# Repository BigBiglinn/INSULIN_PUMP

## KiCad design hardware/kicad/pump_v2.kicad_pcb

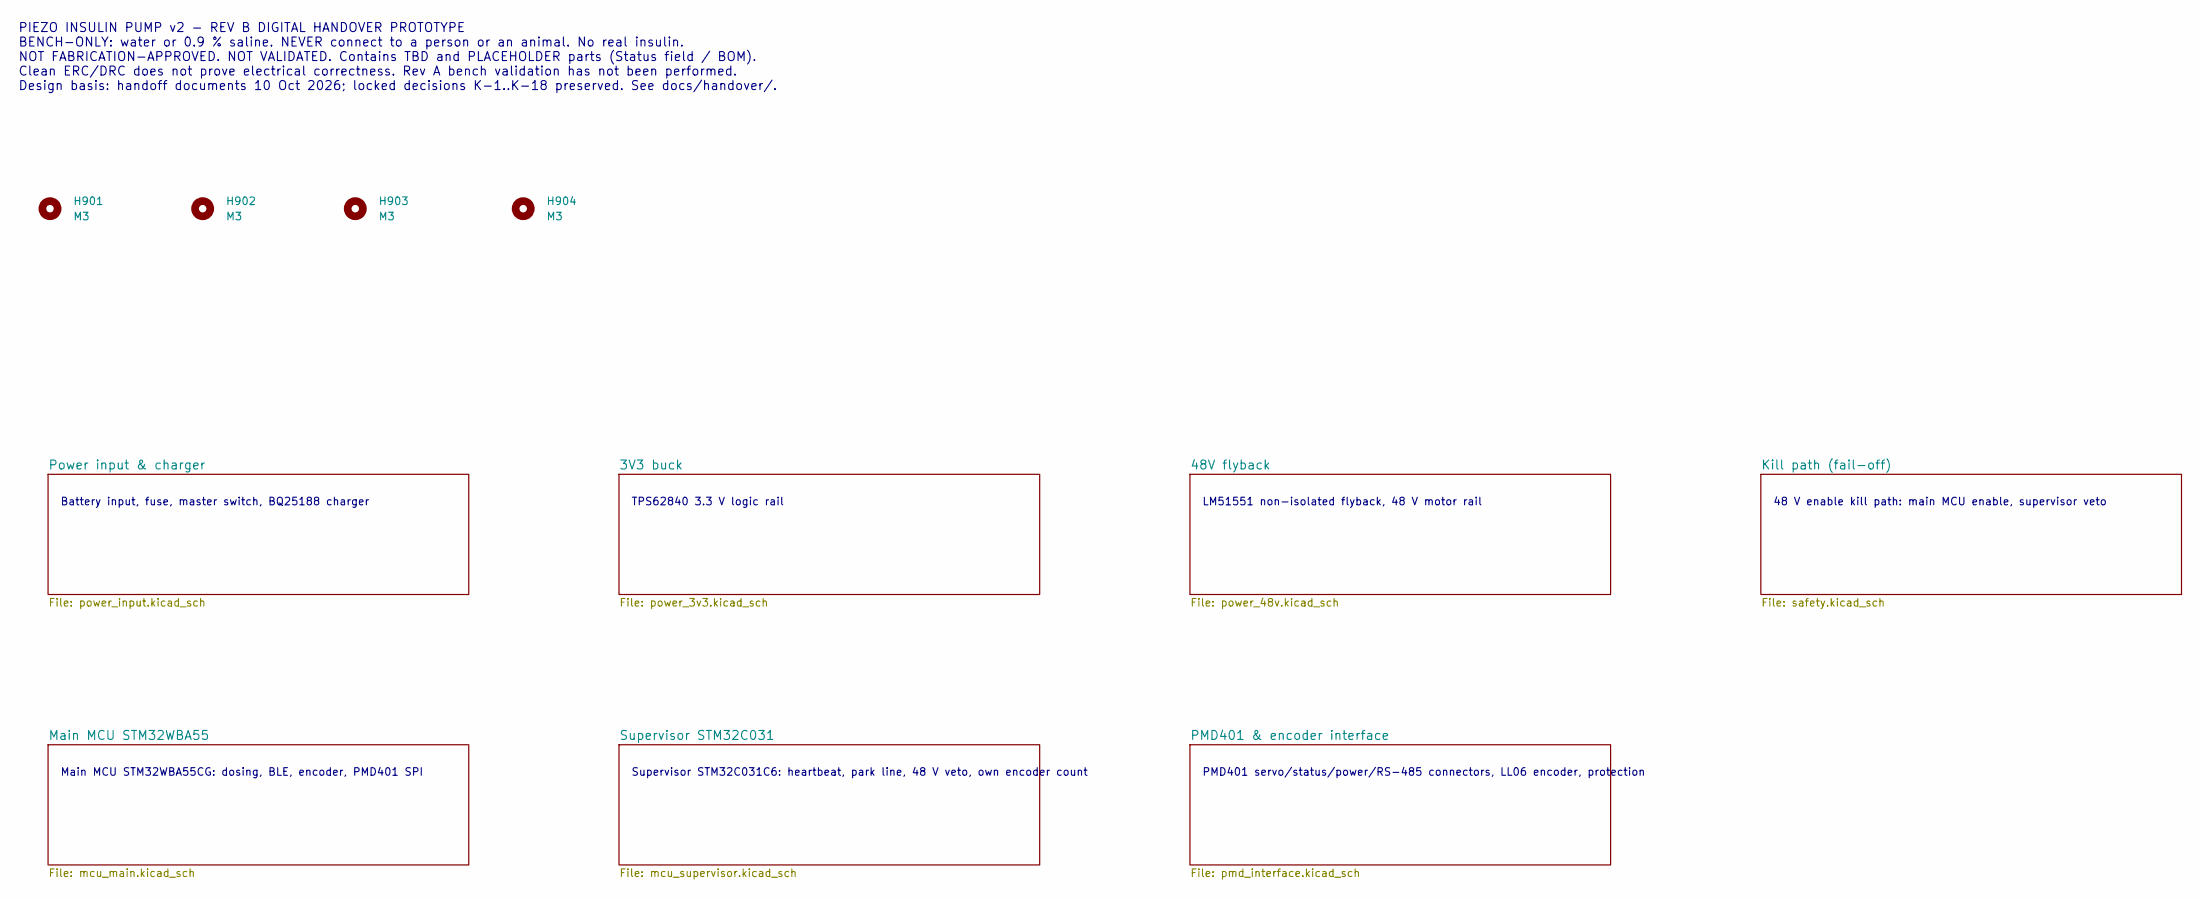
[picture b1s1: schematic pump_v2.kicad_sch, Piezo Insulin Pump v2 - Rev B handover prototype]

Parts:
H901, H902, H903, H904: M3; MountingHole_3.2mm_M3

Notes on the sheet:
PIEZO INSULIN PUMP v2 - REV B DIGITAL HANDOVER PROTOTYPE BENCH-ONLY: water or 0.9 % saline. NEVER connect to a person or an animal. No real insulin. NOT FABRICATION-APPROVED. NOT VALIDATED. Contains TBD and PLACEHOLDER parts (Status field / BOM). Clean ERC/DRC does not prove electrical correctness.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
Battery input, fuse, master switch, BQ25188 charger
TPS62840 3.3 V logic rail
LM51551 non-isolated flyback, 48 V motor rail
48 V enable kill path: main MCU enable, supervisor veto
Main MCU STM32WBA55CG: dosing, BLE, encoder, PMD401 SPI
Supervisor STM32C031C6: heartbeat, park line, 48 V veto, own encoder count
PMD401 servo/status/power/RS-485 connectors, LL06 encoder, protection

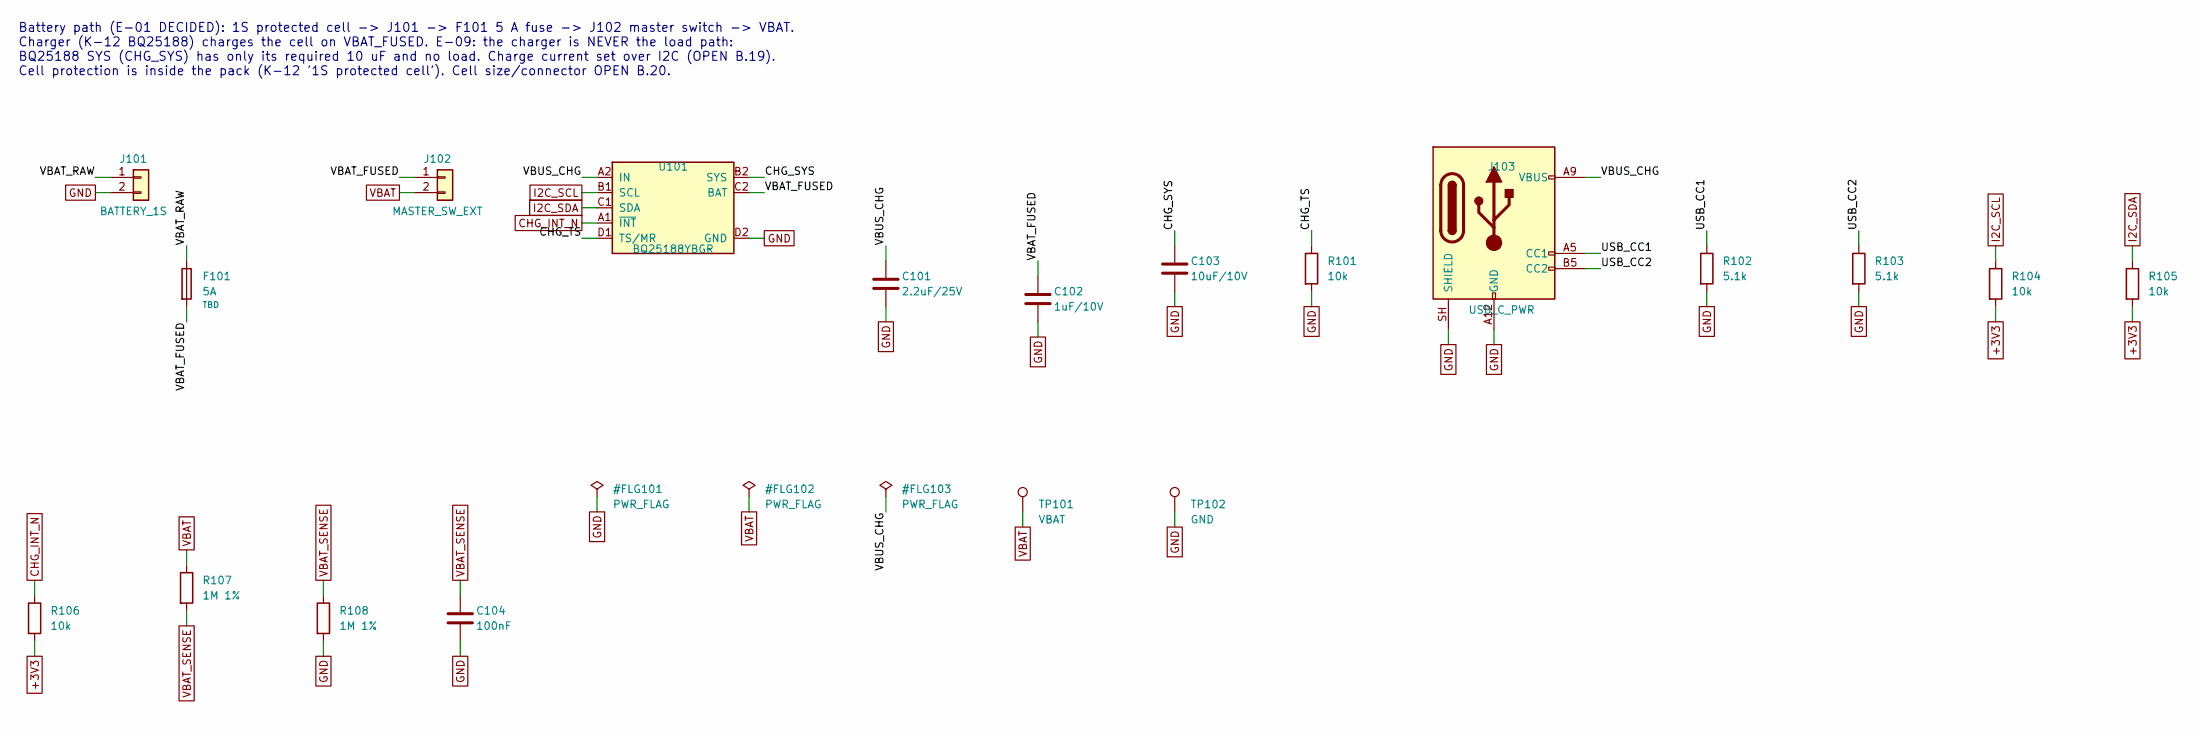
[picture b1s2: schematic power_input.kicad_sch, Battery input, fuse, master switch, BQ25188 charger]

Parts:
C101: 2.2uF/25V; C_0805_2012Metric
C102: 1uF/10V; C_0603_1608Metric
C103: 10uF/10V; C_0805_2012Metric
C104: 100nF; C_0603_1608Metric
F101: 5A; Fuse_2920_7451Metric
J101: BATTERY_1S; AMASS_XT30PW-M_1x02_P2.50mm_Horizontal; MPN AMASS XT30PW-M
J102: MASTER_SW_EXT; TerminalBlock_Phoenix_MKDS-1,5-2-5.08_1x02_P5.08mm_Horizont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
J103: USB_C_PWR; USB_C_Receptacle_GCT_USB4125-xx-x_6P_TopMnt_Horizontal; MPN GCT USB4125
R101, R104, R105, R106: 10k; R_0603_1608Metric
R102, R103: 5.1k; R_0603_1608Metric
R107, R108: 1M 1%; R_0603_1608Metric
TP101: VBAT; TestPoint_Pad_D1.0mm
TP102: GND; TestPoint_Pad_D1.0mm
U101: BQ25188YBGR; TI_YBG0008_DSBGA-8_P0.4mm; MPN BQ25188YBGR

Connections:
+3V3: R104.2, R105.2, R106.2; also elsewhere on the board
/Power input & charger/CHG_SYS: C103.1, U101.B2 (SYS)
/Power input & charger/CHG_TS: R101.1, U101.D1 (TS/MR)
/Power input & charger/USB_CC1: J103.A5 (CC1), R102.1
/Power input & charger/USB_CC2: J103.B5 (CC2), R103.1
/Power input & charger/VBAT_FUSED: C102.1, F101.2, J102.1, U101.C2 (BAT)
/Power input & charger/VBAT_RAW: F101.1, J101.1
/Power input & charger/VBUS_CHG: C101.1, J103.A9 (VBUS), J103.B9 (VBUS), U101.A2 (IN)
CHG_INT_N: R106.1, U101.A1 (~INT); also elsewhere on the board
I2C_SCL: R104.1, U101.B1 (SCL); also elsewhere on the board
I2C_SDA: R105.1, U101.C1 (SDA); also elsewhere on the board
VBAT_SENSE: C104.1, R107.2, R108.1; also elsewhere on the board

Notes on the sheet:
Battery path (E-01 DECIDED): 1S protected cell -> J101 -> F101 5 A fuse -> J102 master switch -> VBAT. Charger (K-12 BQ25188) charges the cell on VBAT_FUSED. E-09: the charger is NEVER the load path: BQ25188 SYS (CHG_SYS) has only its required 10 uF and no load. Charge current set over I2C (OPEN B.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

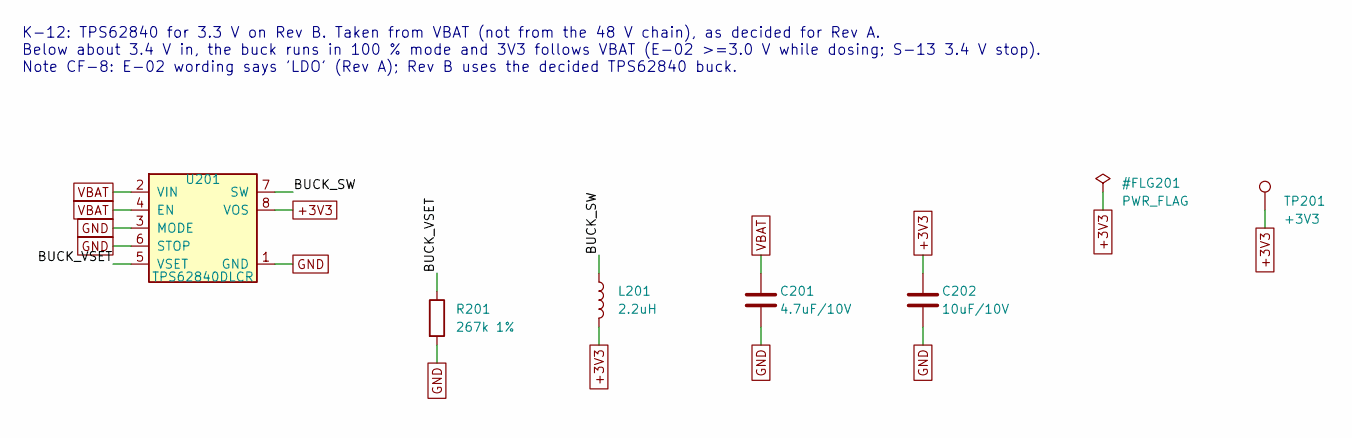
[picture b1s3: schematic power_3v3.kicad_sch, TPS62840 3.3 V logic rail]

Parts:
C201: 4.7uF/10V; C_0603_1608Metric
C202: 10uF/10V; C_0805_2012Metric
L201: 2.2uH; L_0603_1608Metric
R201: 267k 1%; R_0603_1608Metric
TP201: +3V3; TestPoint_Pad_D1.0mm
U201: TPS62840DLCR; Texas_VSON-HR-8_1.5x2mm_P0.5mm; MPN TPS62840DLCR

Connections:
+3V3: C202.1, L201.2, TP201.1, U201.8 (VOS); also elsewhere on the board
/3V3 buck/BUCK_SW: L201.1, U201.7 (SW)
/3V3 buck/BUCK_VSET: R201.1, U201.5 (VSET)

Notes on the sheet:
K-12: TPS62840 for 3.3 V on Rev B. Taken from VBAT (not from the 48 V chain), as decided for Rev A. Below about 3.4 V in, the buck runs in 100 % mode and 3V3 follows VBAT (E-02 >=3.0 V while dosing; S-13 3.4 V stop). Note CF-8: E-02 wording says 'LDO' (Rev A); Rev B uses the decided TPS62840 buck.

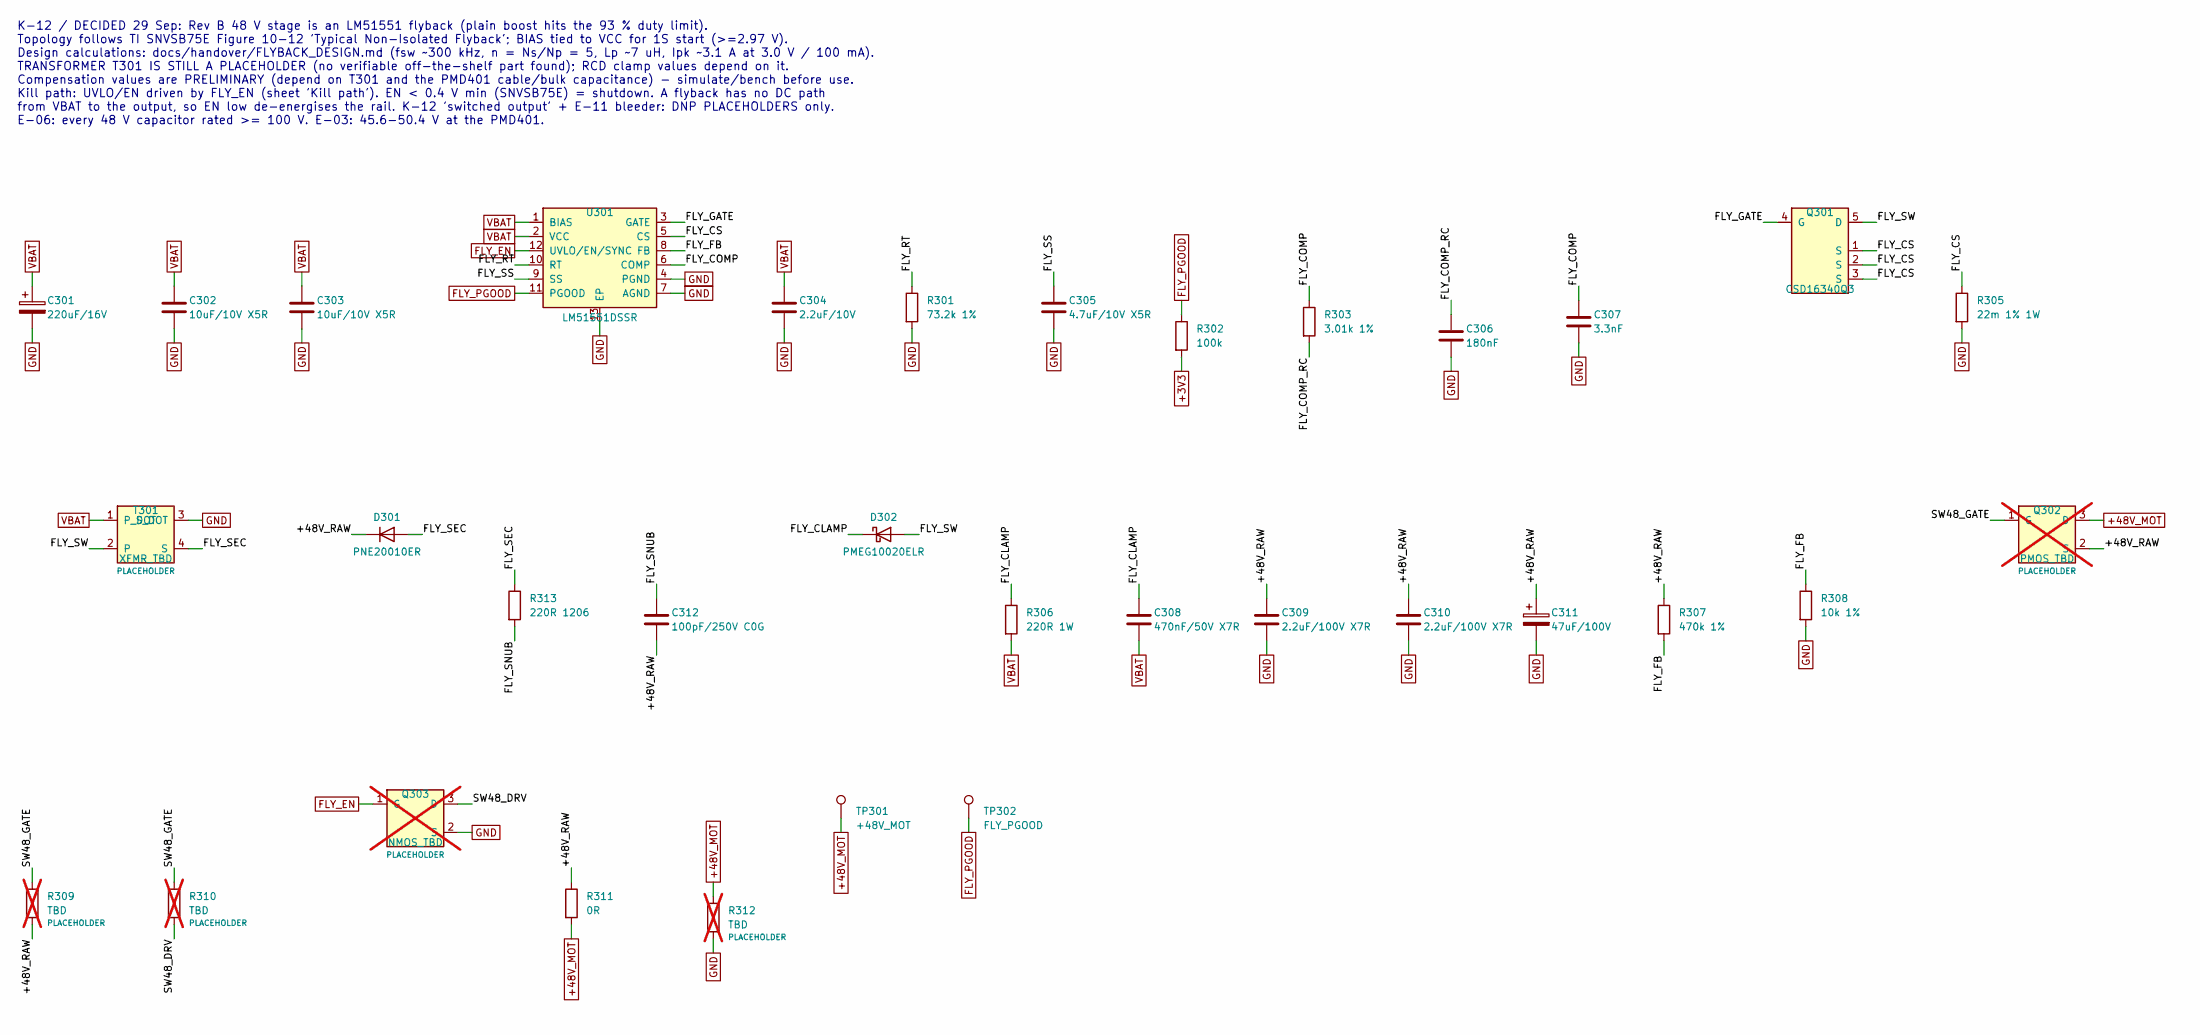
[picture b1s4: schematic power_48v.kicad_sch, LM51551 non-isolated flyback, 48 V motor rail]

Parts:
C301: 220uF/16V; CP_Radial_D8.0mm_P3.50mm
C302, C303: 10uF/10V X5R; C_0805_2012Metric
C304: 2.2uF/10V; C_0603_1608Metric
C305: 4.7uF/10V X5R; C_0603_1608Metric
C306: 180nF; C_0603_1608Metric
C307: 3.3nF; C_0603_1608Metric
C308: 470nF/50V X7R; C_0805_2012Metric
C309, C310: 2.2uF/100V X7R; C_1210_3225Metric
C311: 47uF/100V; CP_Radial_D10.0mm_P5.00mm
C312: 100pF/250V C0G; C_1206_3216Metric
D301: PNE20010ER; Nexperia_CFP3_SOD-123W; MPN Nexperia PNE20010ER
D302: PMEG10020ELR; Nexperia_CFP3_SOD-123W; MPN Nexperia PMEG10020ELR
Q301: CSD16340Q3; VSON-8_3.3x3.3mm_P0.65mm_NexFET; MPN TI CSD16340Q3
Q302: PMOS_TBD; SOT-223-3_TabPin2; not fitted
Q303: NMOS_TBD; SOT-223-3_TabPin2; not fitted
R301: 73.2k 1%; R_0603_1608Metric
R302: 100k; R_0603_1608Metric
R303: 3.01k 1%; R_0603_1608Metric
R305: 22m 1% 1W; R_2512_6332Metric
R306: 220R 1W; R_2512_6332Metric
R307: 470k 1%; R_0603_1608Metric
R308: 10k 1%; R_0603_1608Metric
R309, R310: TBD; R_0603_1608Metric; not fitted
R311: 0R; R_1206_3216Metric
R312: TBD; R_2512_6332Metric; not fitted
R313: 220R 1206; R_1206_3216Metric
T301: XFMR_TBD; XFMR_PLACEHOLDER_4P
TP301: +48V_MOT; TestPoint_Pad_D1.0mm
TP302: FLY_PGOOD; TestPoint_Pad_D1.0mm
U301: LM51551DSSR; WSON-12-1EP_3x2mm_P0.5mm_EP1x2.65; MPN LM51551DSSR

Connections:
+3V3: R302.2; also elsewhere on the board
/48V flyback/FLY_CLAMP: C308.1, D302.1 (K), R306.1; also elsewhere on the board
/48V flyback/FLY_COMP: C307.1, R303.1, U301.6 (COMP)
/48V flyback/FLY_COMP_RC: C306.1, R303.2
/48V flyback/FLY_CS: Q301.1 (S), Q301.2 (S), Q301.3 (S), R305.1, U301.5 (CS)
/48V flyback/FLY_FB: R307.2, R308.1, U301.8 (FB)
/48V flyback/FLY_RT: R301.1, U301.10 (RT)
/48V flyback/FLY_SEC_C: T301.5, T301.9
/48V flyback/FLY_SEC_D: T301.6, T301.8
/48V flyback/FLY_SNUB: C312.1, R313.2
/48V flyback/FLY_SS: C305.1, U301.9 (SS)
FLY_EN: Q303.1 (G), U301.12 (UVLO/EN/SYNC); also elsewhere on the board
FLY_PGOOD: R302.1, TP302.1, U301.11 (PGOOD); also elsewhere on the board
unnamed: Q302.1 (G), R309.1, R310.1
unnamed: Q303.3 (D), R310.2

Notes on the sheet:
K-12 / DECIDED 29 Sep: Rev B 48 V stage is an LM51551 flyback (plain boost hits the 93 % duty limit). Topology follows TI SNVSB75E Figure 10-12 'Typical Non-Isolated Flyback'; BIAS tied to VCC for 1S start (>=2.97 V). Design calculations: docs/handover/FLYBACK_DESIGN.md (fsw ~300 kHz, n = Ns/Np = 5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

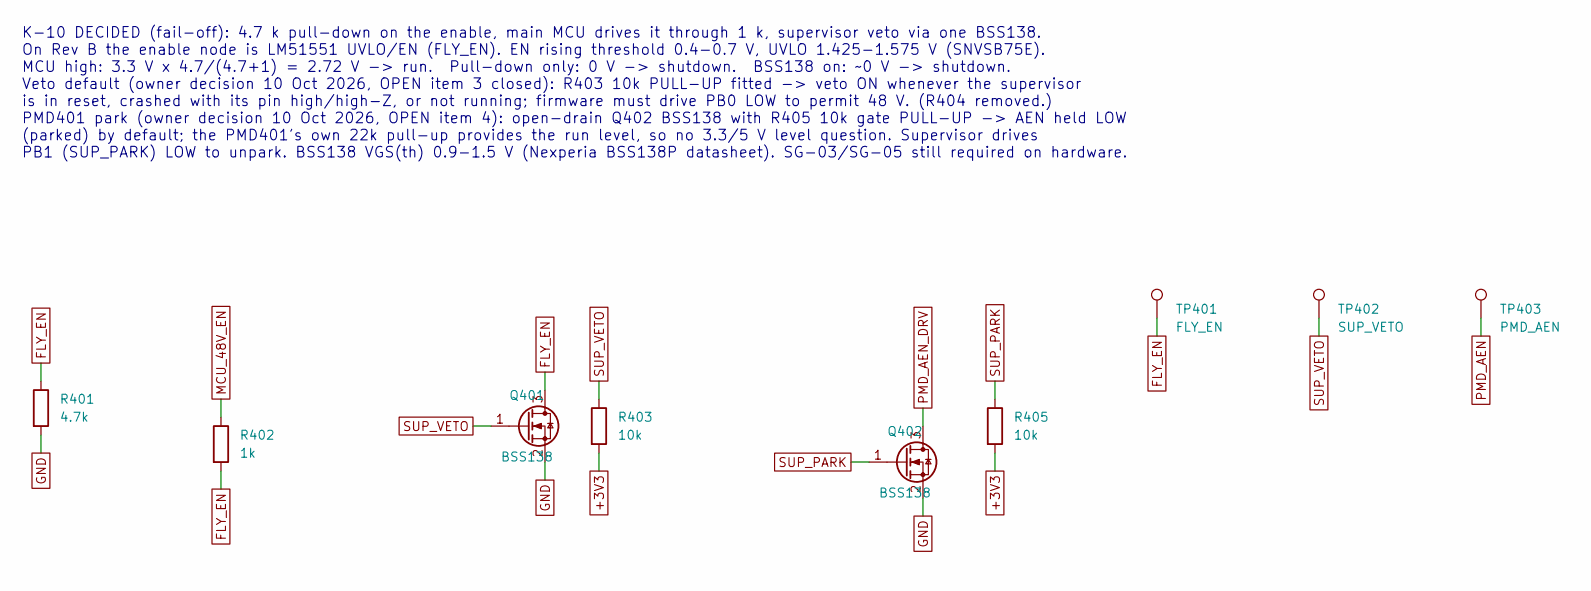
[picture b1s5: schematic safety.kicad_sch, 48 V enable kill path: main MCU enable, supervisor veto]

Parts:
Q401: BSS138; SOT-23; MPN BSS138
Q402: BSS138; SOT-23; MPN BSS138 (e.g. Nexperia BSS138P)
R401: 4.7k; R_0603_1608Metric
R402: 1k; R_0603_1608Metric
R403, R405: 10k; R_0603_1608Metric
TP401: FLY_EN; TestPoint_Pad_D1.0mm
TP402: SUP_VETO; TestPoint_Pad_D1.0mm
TP403: PMD_AEN; TestPoint_Pad_D1.0mm

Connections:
+3V3: R403.2, R405.2; also elsewhere on the board
FLY_EN: Q401.3 (D), R401.1, R402.2, TP401.1; also elsewhere on the board
MCU_48V_EN: R402.1; also elsewhere on the board
PMD_AEN: TP403.1; also elsewhere on the board
PMD_AEN_DRV: Q402.3 (D); also elsewhere on the board
SUP_PARK: Q402.1 (G), R405.1; also elsewhere on the board
SUP_VETO: Q401.1 (G), R403.1, TP402.1; also elsewhere on the board

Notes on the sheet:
K-10 DECIDED (fail-off): 4.7 k pull-down on the enable, main MCU drives it through 1 k, supervisor veto via one BSS138. On Rev B the enable node is LM51551 UVLO/EN (FLY_EN). EN rising threshold 0.4-0.7 V, UVLO 1.425-1.575 V (SNVSB75E). MCU high: 3.3 V x 4.7/(4.7+1) = 2.72 V -> run. Pull-down only: 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

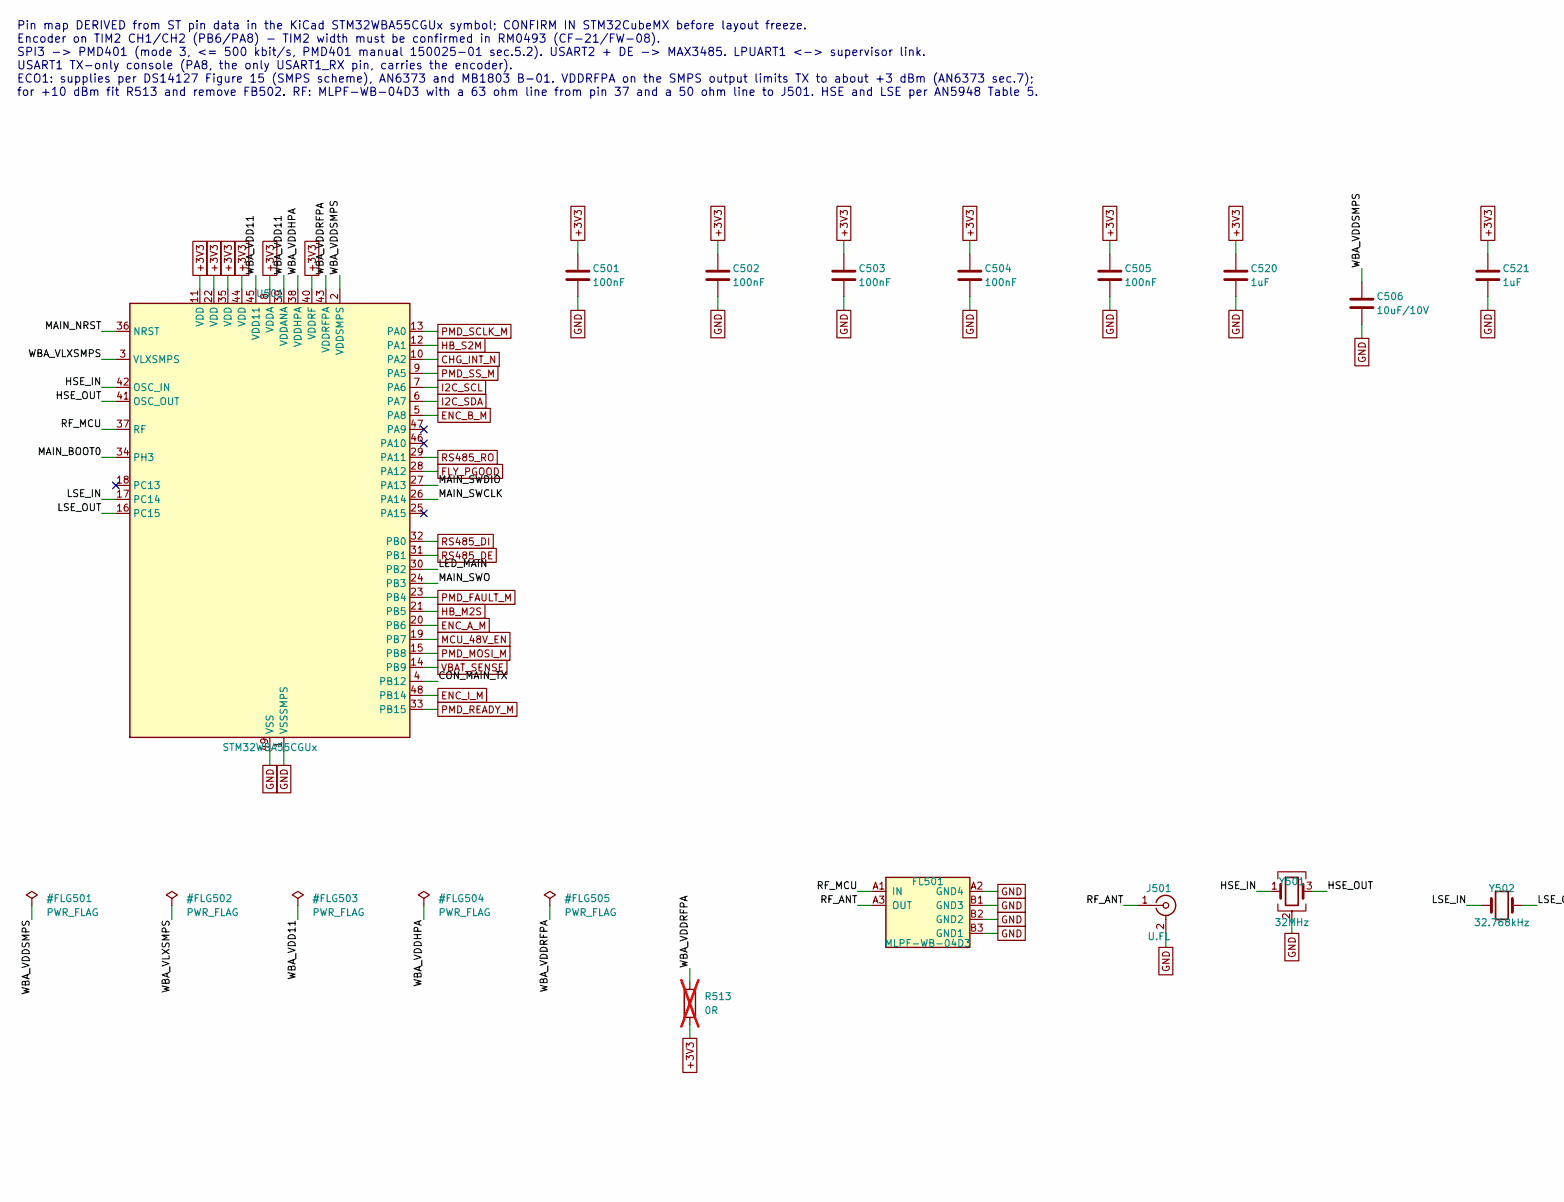
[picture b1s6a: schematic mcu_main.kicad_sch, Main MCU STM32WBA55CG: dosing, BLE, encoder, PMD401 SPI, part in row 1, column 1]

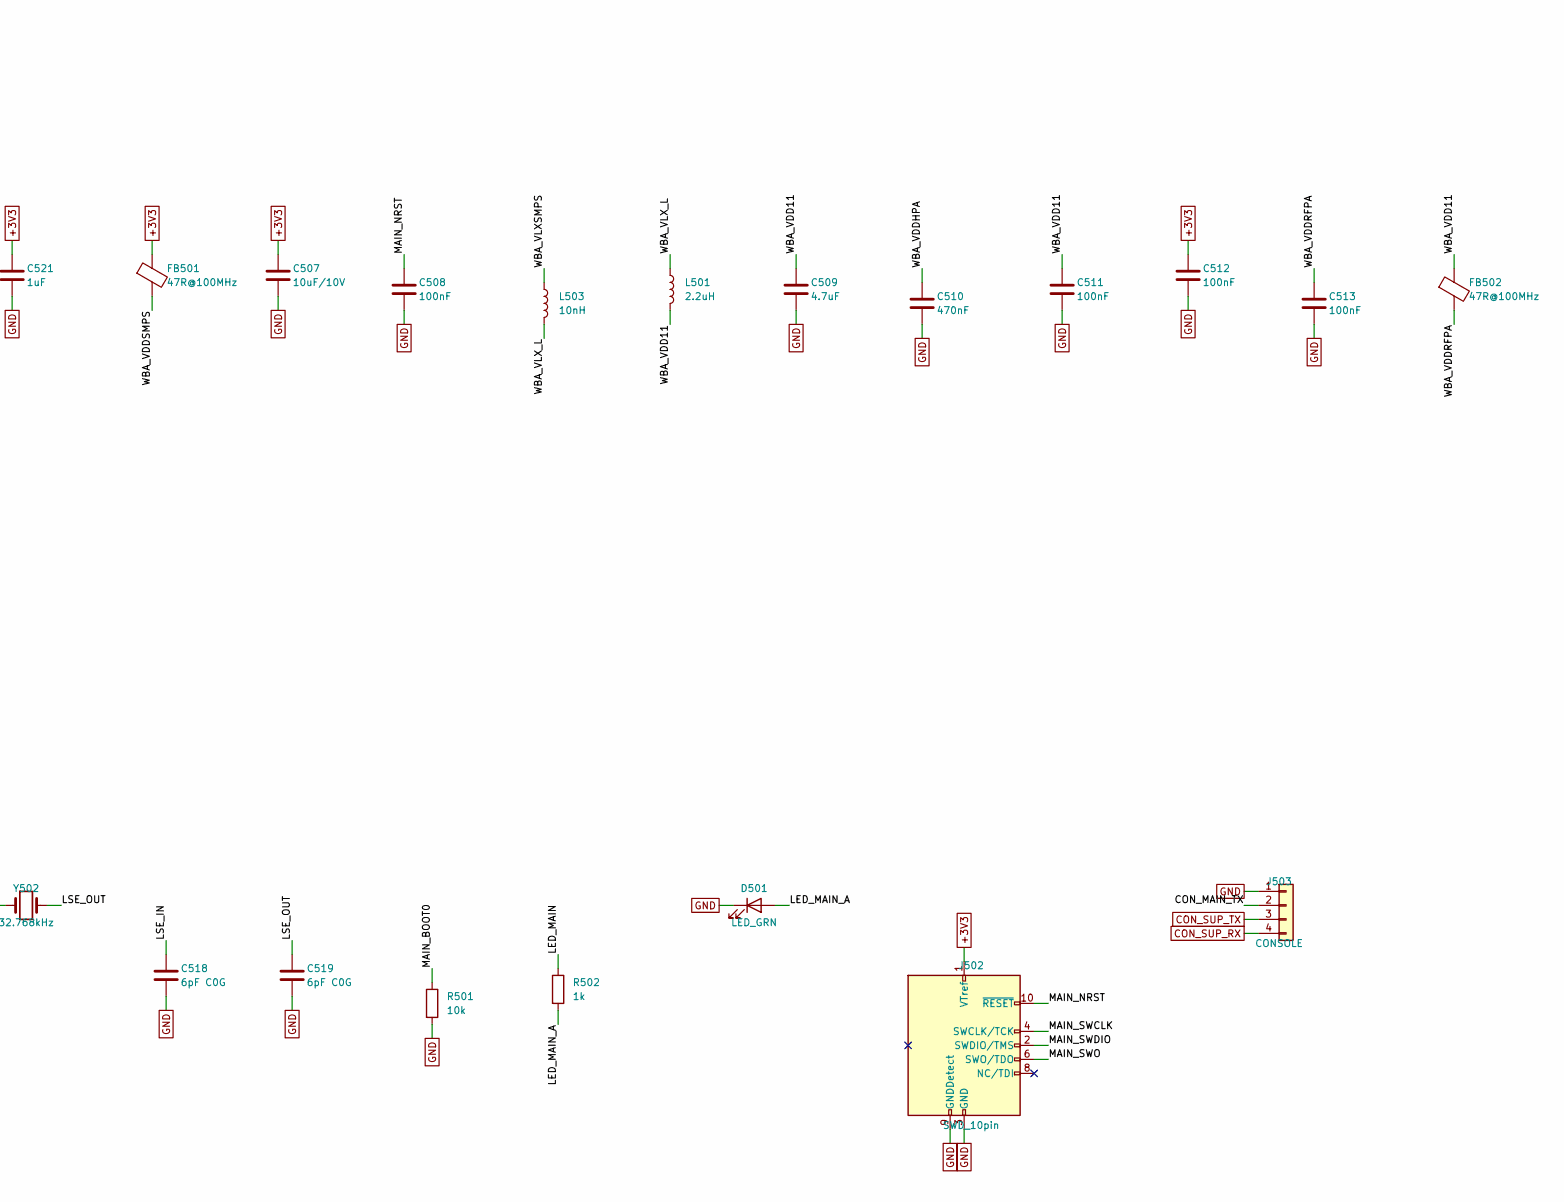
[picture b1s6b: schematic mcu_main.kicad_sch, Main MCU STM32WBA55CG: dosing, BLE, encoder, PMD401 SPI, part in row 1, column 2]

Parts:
C501, C502, C503, C504, C505, C508: 100nF; C_0603_1608Metric
C506: 10uF/10V; C_0603_1608Metric; MPN Murata GRM188C81A106MA73
C507: 10uF/10V; C_0805_2012Metric
C509: 4.7uF; C_0402_1005Metric; MPN Murata GRM155R60J475ME47D
C510: 470nF; C_0402_1005Metric
C511, C512, C513: 100nF; C_0402_1005Metric
C518, C519: 6pF C0G; C_0402_1005Metric
C520, C521: 1uF; C_0603_1608Metric
D501: LED_GRN; LED_0603_1608Metric
FB501, FB502: 47R@100MHz; C_0603_1608Metric; MPN Taiyo Yuden LSMGA160808T470RG
FL501: MLPF-WB-04D3; ST_MLPF-WB-04D3; MPN ST MLPF-WB-04D3
J501: U.FL; U.FL_Hirose_U.FL-R-SMT-1_Vertical; MPN Hirose U.FL-R-SMT-1
J502: SWD_10pin; PinHeader_2x05_P1.27mm_Vertical
J503: CONSOLE; PinHeader_1x04_P2.54mm_Vertical
L501: 2.2uH; L_0805_2012Metric; MPN Murata LQM21PN2R2MGH
L503: 10nH; L_0402_1005Metric; MPN Murata LQG15HS10NJ02D
R501: 10k; R_0603_1608Metric
R502: 1k; R_0603_1608Metric
R513: 0R; R_0603_1608Metric; not fitted
U501: STM32WBA55CGUx; QFN-48-1EP_7x7mm_P0.5mm_EP5.6x5.6mm; MPN STM32WBA55CGU6 (temp suffix TBD)
Y501: 32MHz; Crystal_NX1612SA; MPN NDK NX1612SA-32MHZ-EXS00A-CS09166
Y502: 32.768kHz; Crystal_NX1610SE; MPN NDK NX1610SE-32.768KHZ-EXS00A-MU01501

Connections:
+3V3: C501.1, C502.1, C503.1, C504.1, C505.1, C507.1, C512.1, C520.1, C521.1, FB501.1, J502.1 (VTref), R513.2, U501.8 (VDDA), U501.11 (VDD), U501.22 (VDD), U501.35 (VDD), U501.40 (VDDRF), U501.44 (VDD); also elsewhere on the board
/Main MCU STM32WBA55/CON_MAIN_TX: J503.2, U501.4 (PB12)
/Main MCU STM32WBA55/HSE_IN: U501.42 (OSC_IN), Y501.1
/Main MCU STM32WBA55/HSE_OUT: U501.41 (OSC_OUT), Y501.3
/Main MCU STM32WBA55/LED_MAIN: R502.1, U501.30 (PB2)
/Main MCU STM32WBA55/LED_MAIN_A: D501.2 (A), R502.2
/Main MCU STM32WBA55/LSE_IN: C518.1, U501.17 (PC14), Y502.1
/Main MCU STM32WBA55/LSE_OUT: C519.1, U501.16 (PC15), Y502.2
/Main MCU STM32WBA55/MAIN_BOOT0: R501.1, U501.34 (PH3)
/Main MCU STM32WBA55/MAIN_NRST: C508.1, J502.10 (~RESET), U501.36 (NRST)
/Main MCU STM32WBA55/MAIN_SWCLK: J502.4 (SWCLK/TCK), U501.26 (PA14)
/Main MCU STM32WBA55/MAIN_SWDIO: J502.2 (SWDIO/TMS), U501.27 (PA13)
/Main MCU STM32WBA55/MAIN_SWO: J502.6 (SWO/TDO), U501.24 (PB3)
/Main MCU STM32WBA55/RF_ANT: FL501.A3 (OUT), J501.1 (In)
/Main MCU STM32WBA55/RF_MCU: FL501.A1 (IN), U501.37 (RF)
/Main MCU STM32WBA55/WBA_VDD11: C509.1, C511.1, FB502.1, L501.2, U501.39 (VDDANA), U501.45 (VDD11)
/Main MCU STM32WBA55/WBA_VDDHPA: C510.1, U501.38 (VDDHPA)
/Main MCU STM32WBA55/WBA_VDDRFPA: C513.1, FB502.2, R513.1, U501.43 (VDDRFPA)
/Main MCU STM32WBA55/WBA_VDDSMPS: C506.1, FB501.2, U501.2 (VDDSMPS)
/Main MCU STM32WBA55/WBA_VLXSMPS: L503.1, U501.3 (VLXSMPS)
/Main MCU STM32WBA55/WBA_VLX_L: L501.1, L503.2
CHG_INT_N: U501.10 (PA2); also elsewhere on the board
CON_SUP_RX: J503.4; also elsewhere on the board
CON_SUP_TX: J503.3; also elsewhere on the board
ENC_A_M: U501.20 (PB6); also elsewhere on the board
ENC_B_M: U501.5 (PA8); also elsewhere on the board
ENC_I_M: U501.48 (PB14); also elsewhere on the board
FLY_PGOOD: U501.28 (PA12); also elsewhere on the board
HB_M2S: U501.21 (PB5); also elsewhere on the board
HB_S2M: U501.12 (PA1); also elsewhere on the board
I2C_SCL: U501.7 (PA6); also elsewhere on the board
I2C_SDA: U501.6 (PA7); also elsewhere on the board
MCU_48V_EN: U501.19 (PB7); also elsewhere on the board
PMD_FAULT_M: U501.23 (PB4); also elsewhere on the board
PMD_MOSI_M: U501.15 (PB8); also elsewhere on the board
PMD_READY_M: U501.33 (PB15); also elsewhere on the board
PMD_SCLK_M: U501.13 (PA0); also elsewhere on the board
PMD_SS_M: U501.9 (PA5); also elsewhere on the board
RS485_DE: U501.31 (PB1); also elsewhere on the board
RS485_DI: U501.32 (PB0); also elsewhere on the board
RS485_RO: U501.29 (PA11); also elsewhere on the board
VBAT_SENSE: U501.14 (PB9); also elsewhere on the board

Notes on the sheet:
Pin map DERIVED from ST pin data in the KiCad STM32WBA55CGUx symbol; CONFIRM IN STM32CubeMX before layout freeze. Encoder on TIM2 CH1/CH2 (PB6/PA8) - TIM2 width must be confirmed in RM0493 (CF-21/FW-08). SPI3 -> PMD401 (mode 3, <= 500 kbit/s, PMD401 manual 150025-01 sec.5.2). USART2 + DE -> MAX3485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

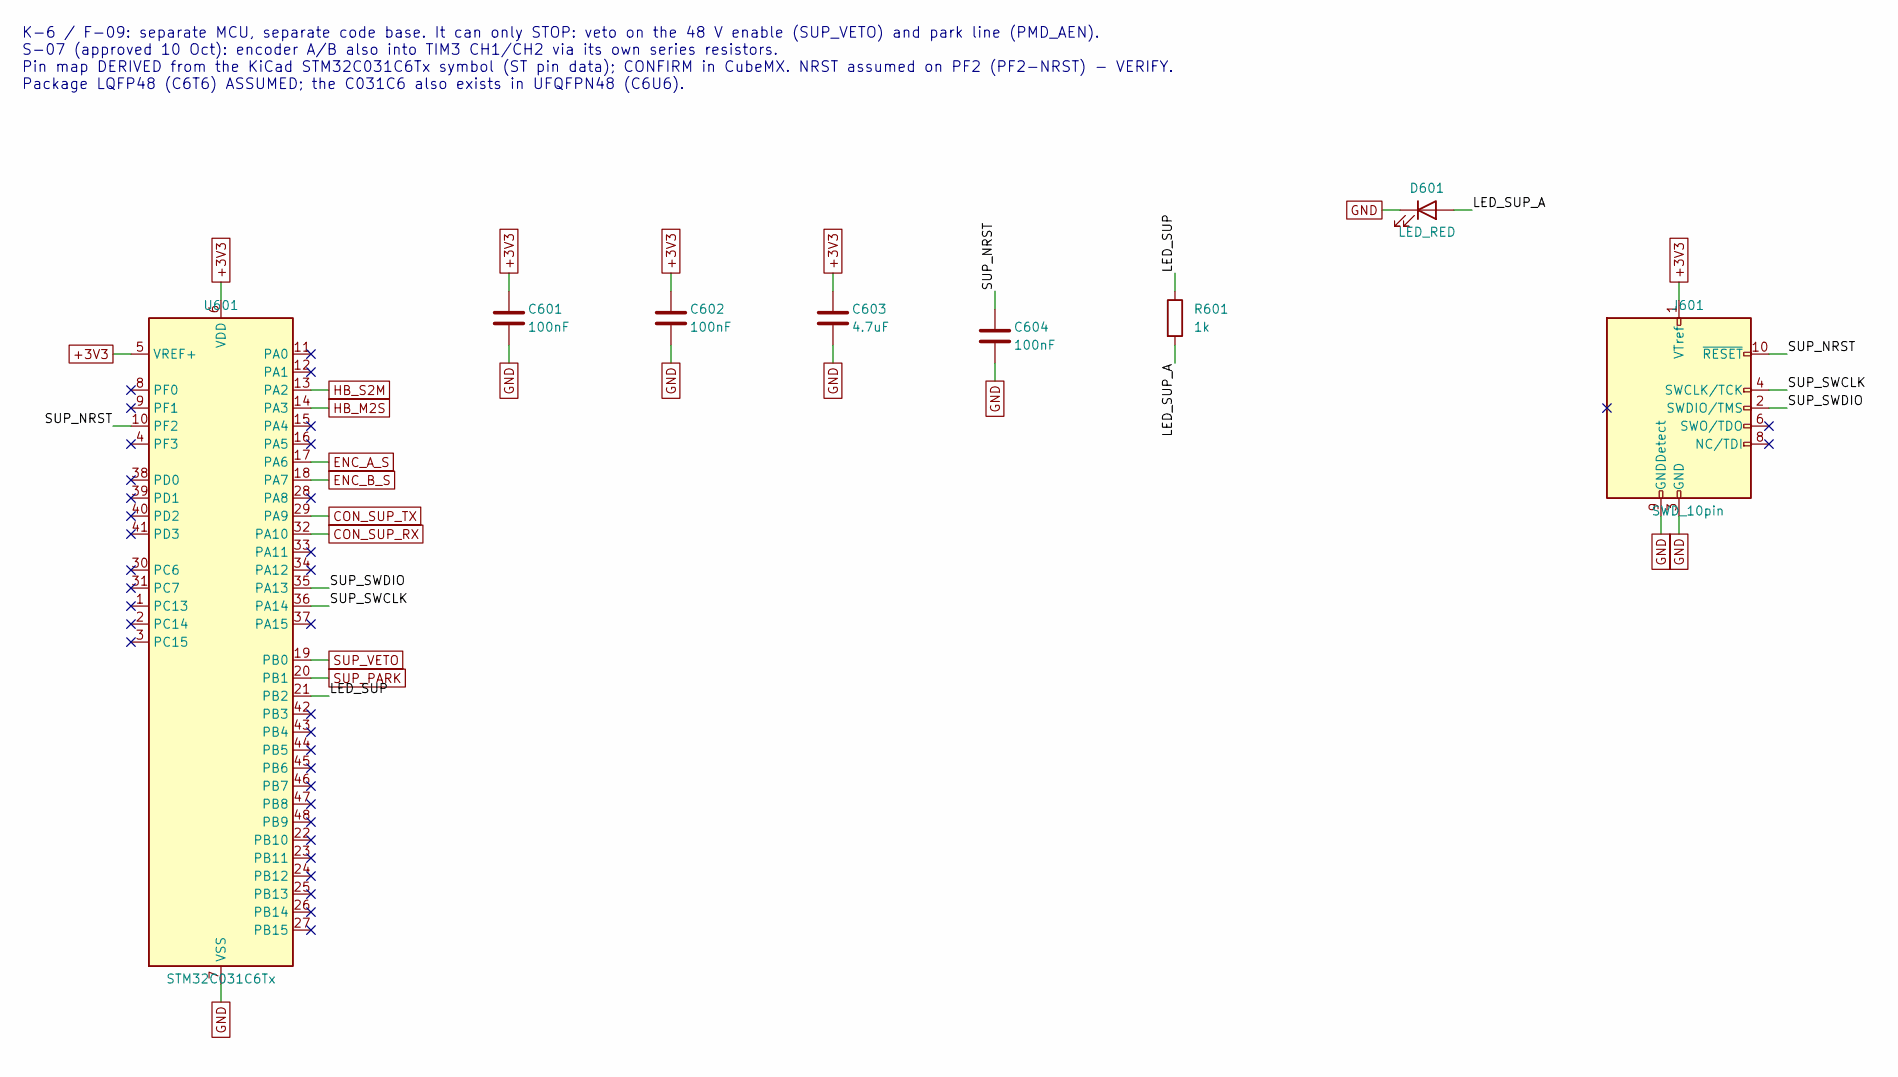
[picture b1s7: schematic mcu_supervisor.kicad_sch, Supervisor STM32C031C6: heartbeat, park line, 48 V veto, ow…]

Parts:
C601, C602, C604: 100nF; C_0603_1608Metric
C603: 4.7uF; C_0603_1608Metric
D601: LED_RED; LED_0603_1608Metric
J601: SWD_10pin; PinHeader_2x05_P1.27mm_Vertical
R601: 1k; R_0603_1608Metric
U601: STM32C031C6Tx; LQFP-48_7x7mm_P0.5mm; MPN STM32C031C6T6 (package ASSUMED)

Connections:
+3V3: C601.1, C602.1, C603.1, J601.1 (VTref), U601.5 (VREF+), U601.6 (VDD); also elsewhere on the board
/Supervisor STM32C031/LED_SUP: R601.1, U601.21 (PB2)
/Supervisor STM32C031/LED_SUP_A: D601.2 (A), R601.2
/Supervisor STM32C031/SUP_NRST: C604.1, J601.10 (~RESET), U601.10 (PF2)
/Supervisor STM32C031/SUP_SWCLK: J601.4 (SWCLK/TCK), U601.36 (PA14)
/Supervisor STM32C031/SUP_SWDIO: J601.2 (SWDIO/TMS), U601.35 (PA13)
CON_SUP_RX: U601.32 (PA10); also elsewhere on the board
CON_SUP_TX: U601.29 (PA9); also elsewhere on the board
ENC_A_S: U601.17 (PA6); also elsewhere on the board
ENC_B_S: U601.18 (PA7); also elsewhere on the board
HB_M2S: U601.14 (PA3); also elsewhere on the board
HB_S2M: U601.13 (PA2); also elsewhere on the board
SUP_PARK: U601.20 (PB1); also elsewhere on the board
SUP_VETO: U601.19 (PB0); also elsewhere on the board

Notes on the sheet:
K-6 / F-09: separate MCU, separate code base. It can only STOP: veto on the 48 V enable (SUP_VETO) and park line (PMD_AEN). S-07 (approved 10 Oct): encoder A/B also into TIM3 CH1/CH2 via its own series resistors. Pin map DERIVED from the KiCad STM32C031C6Tx symbol (ST pin data); CONFIRM in CubeMX. 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
